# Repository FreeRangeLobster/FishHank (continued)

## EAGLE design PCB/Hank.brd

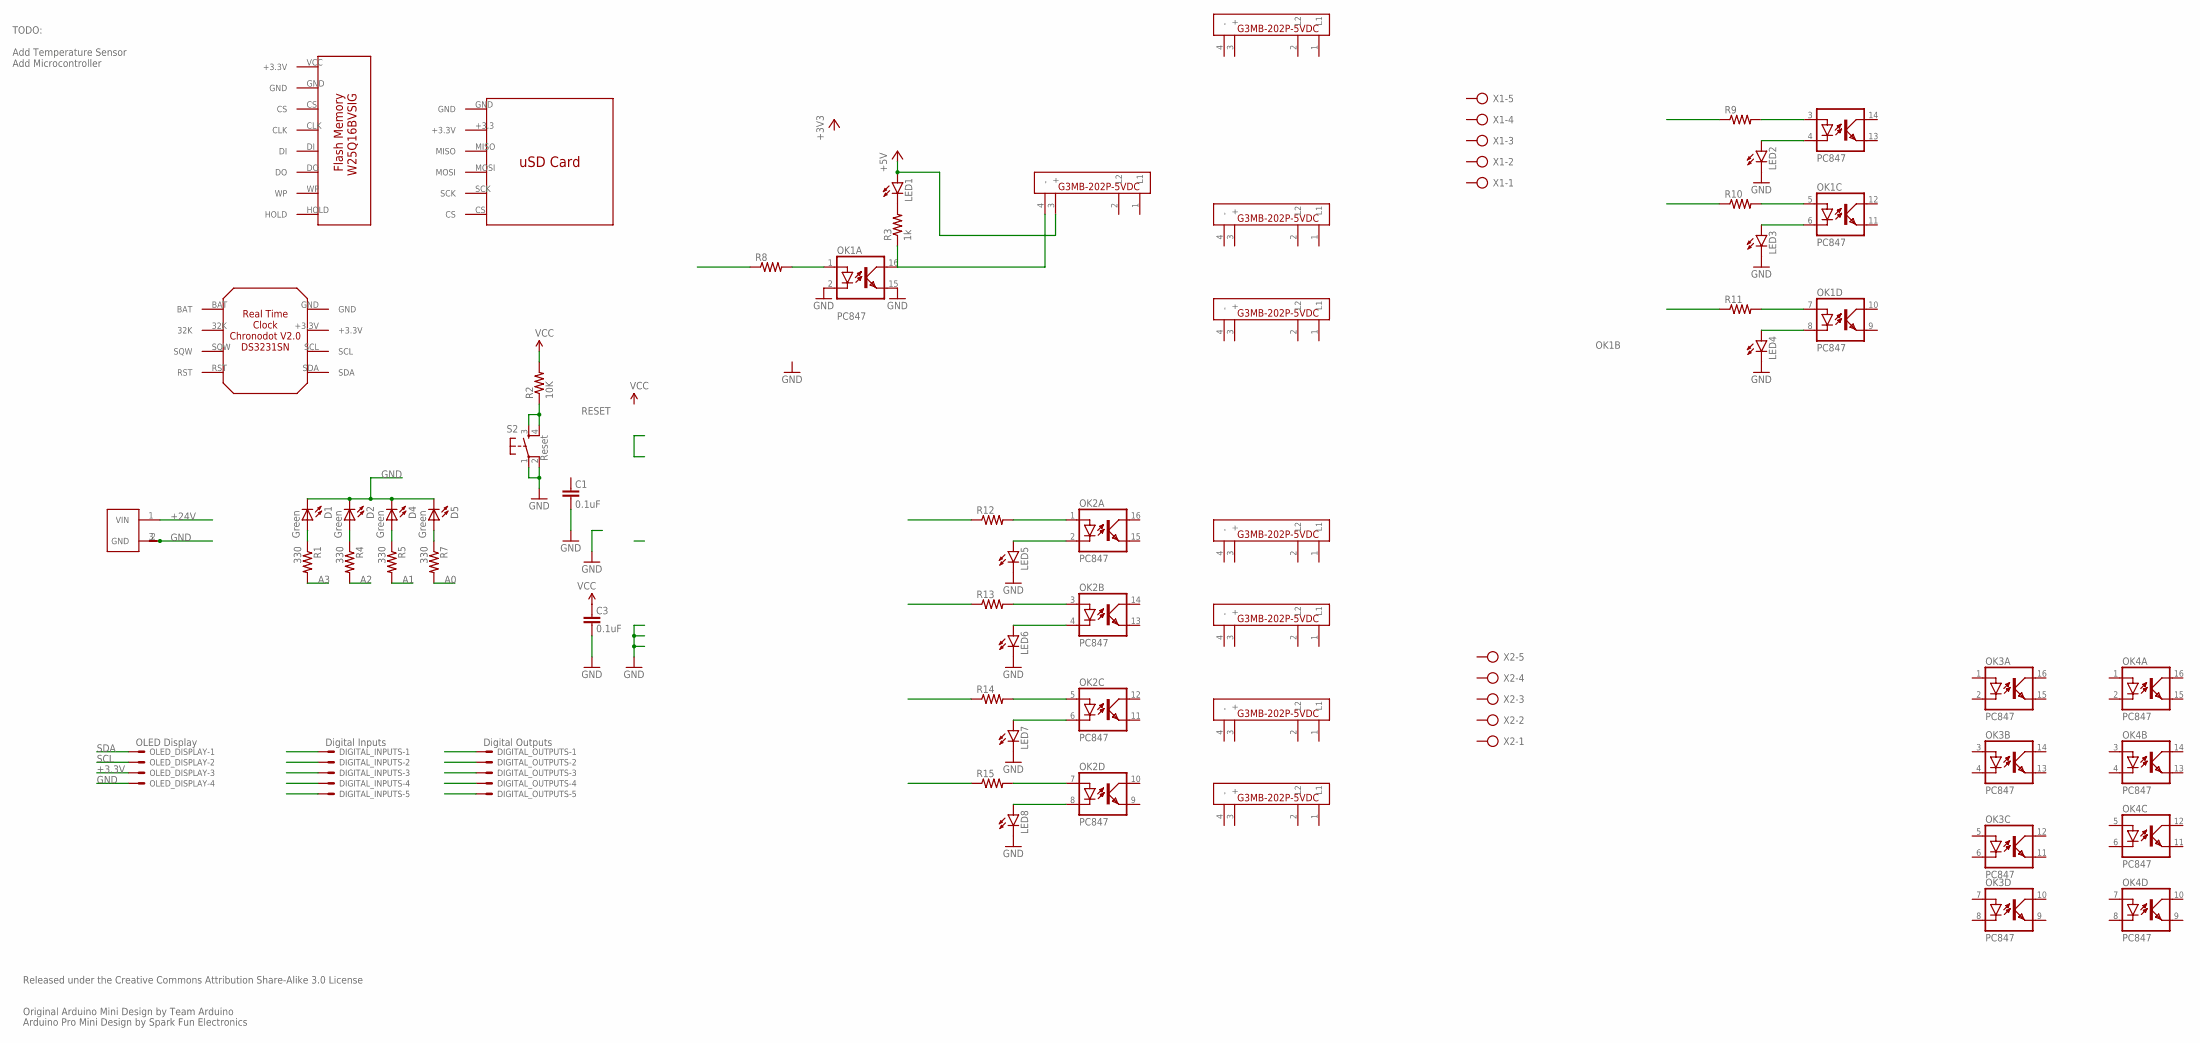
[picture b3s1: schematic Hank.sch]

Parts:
C1, C3: 0.1uF; C0603
D1, D2, D4, D5: Green; LED-0603
DIGITAL_INPUTS: Digital Inputs; 22-23-2051
DIGITAL_OUTPUTS: Digital Outputs; 22-23-2051
LED1, LED2, LED3, LED4, LED5, LED6, LED7, LED8: LED3MM
OK1, OK2, OK3, OK4: PC847; DIL16
OLED_DISPLAY: OLED Display; 22-23-2041
R1, R4, R5, R7: 330; R0603
R2: 10K; R0603
R3: 1k; 0207/10
R8, R9, R10, R11, R12, R13, R14, R15: R-US_0207/10; 0207/10
S2: Reset; TACTILE_SWITCH_SMD
U$1, U$7, U$8, U$9, U$10, U$11, U$12, U$13: SSR; SSR_FOOTPRINT
U$3: BARREL-3.5MM
U$4: FLASH_MEMORY; FLASHMEMORY_FOOTPRINT
U$6: RTC; RTC_FOOTPRINT
U$14: SD_CARD_READER; SD_CARD_READER_FOOTPRINT
X1, X2: AK300/5

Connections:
+3.3V: OLED_DISPLAY.3
+5V: LED1.A, U$7.3 (+)
+24V: U$3.1 (VIN)
A0: R7.2
A1: R5.2
A2: R4.2
A3: R1.2
GND: C1.1, C3.1, D1.C, D2.C, D4.C, D5.C, LED2.K (C), LED3.K (C), LED4.K (C), LED5.K (C), LED6.K (C), LED7.K (C), LED8.K (C), OK1.2 (C), OK1.15 (EMIT), OLED_DISPLAY.4, S2.1, S2.2, U$3.2 (GND__), U$3.3 (GND)
unnamed: D1.A, R1.1
unnamed: D2.A, R4.1
unnamed: D4.A, R5.1
unnamed: D5.A, R7.1
unnamed: LED4.A, OK1.8 (C)
unnamed: OK1.7 (A), R11.2
unnamed: OK1.1 (A), R8.2
unnamed: LED1.K (C), R3.2
unnamed: OK1.3 (A), R9.2
unnamed: LED2.A, OK1.4 (C)
unnamed: OK1.5 (A), R10.2
unnamed: LED3.A, OK1.6 (C)
unnamed: OK2.1 (A), R12.2
unnamed: OK2.3 (A), R13.2
unnamed: OK2.5 (A), R14.2
unnamed: OK2.7 (A), R15.2
unnamed: LED6.A, OK2.4 (C)
unnamed: LED5.A, OK2.2 (C)
unnamed: LED7.A, OK2.6 (C)
unnamed: LED8.A, OK2.8 (C)
unnamed: OK1.16 (COL), R3.1, U$7.4 (-)
RESET: R2.1, S2.3, S2.4
SCL: OLED_DISPLAY.2
SDA: OLED_DISPLAY.1
VCC: C3.2, R2.2

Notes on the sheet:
Released under the Creative Commons Attribution Share-Alike 3.0 License
TODO: Add Temperature Sensor Add Microcontroller
Original Arduino Mini Design by Team Arduino
Arduino Pro Mini Design by Spark Fun Electronics

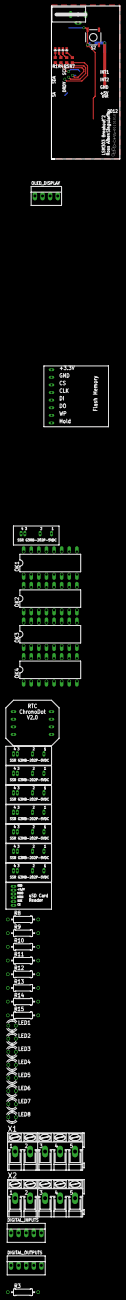
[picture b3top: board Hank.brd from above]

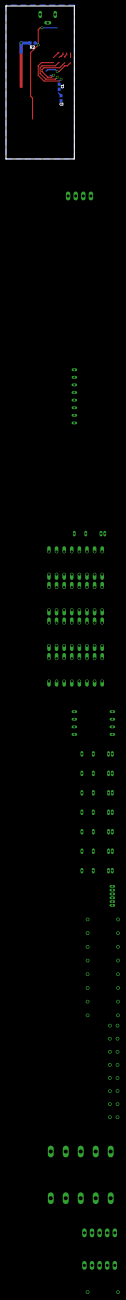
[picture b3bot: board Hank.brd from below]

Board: 2 copper layers, 22.8 x 51.1 mm, 50 parts (3 on the bottom side), 25 nets.

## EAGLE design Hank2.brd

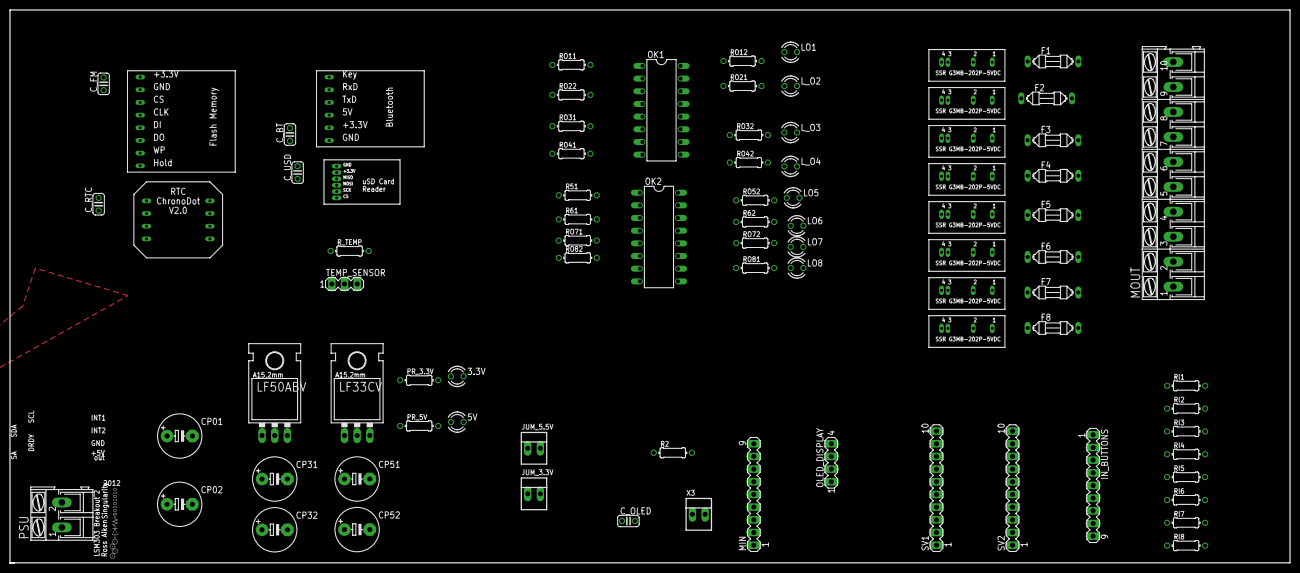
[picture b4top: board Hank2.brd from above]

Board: 2 copper layers, 256.5 x 110.8 mm, 84 parts (0 on the bottom side), 81 nets, no tracks yet.

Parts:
3.3V, 5V: LED3MM
CP01, CP31, CP51: 100u; E5-8,5
CP02, CP32, CP52: 100n; E5-8,5
C_BT: 0.1uF; C025-024X044
C_FM: 0.1uF; C025-024X044
C_OLED: 0.1uF; C025-024X044
C_RTC: 0.1uF; C025-024X044
C_USD: 0.1uF; C025-024X044
F1, F2, F3, F4, F5, F6, F7, F8: SM 092 A0 2A; PICOFUSE
IN_BUTTONS: MA09-1
JUM_3.3V, JUM_5.5V: 22-23-2021
LF33CV, LF50ABV: 78XXL
LO1, LO5, LO6, LO7, LO8: LED3MM
L_O2, L_O3, L_O4: LED3MM
MIN: MA09-1
MOUT: AK300/10
OK1, OK2: PC847; DIL16
OLED_DISPLAY: MA04-1
PR_3.3V, PR_5V: 1k; 0204/7
PSU: AK300/2
R2: 0204/7
R51, R61: 150; 0204/7
R62: 1k; 0204/7
RI1, RI2, RI3, RI4, RI5, RI6, RI7: 330; 0204/7
RI8: 0204/7
RO11, RO21, RO31, RO41, RO71, RO81: 150; 0204/7
RO12, RO22, RO42, RO52, RO72, RO82: 1k; 0204/7
RO32: 0204/7
R_TEMP: 4.7K; 0204/7
SSR1, SSR2, SSR3, SSR4, SSR5, SSR6, SSR7, SSR8: SSR; SSR_FOOTPRINT
SV1, SV2: MA10-1
TEMP_SENSOR: MA03-1
U$1: FLASH_MEMORY; FLASHMEMORY_FOOTPRINT
U$4: BLUETOOTH; BLUETOOTH_FOOTPRINT
U$6: RTC; RTC_FOOTPRINT
U$7: SD_CARD_READER; SD_CARD_READER_FOOTPRINT
X3: Auto_Manual; 22-23-2021

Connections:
+3V3: 3.3V.A, CP31.+, CP32.+, C_BT.1, C_FM.1, C_OLED.1, C_RTC.2, C_USD.1, IN_BUTTONS.1, JUM_5.5V.1, LF33CV.OUT, OLED_DISPLAY.3, R_TEMP.2, TEMP_SENSOR.3, U$1.HOLD, U$1.VCC, U$1.WP, U$4.+3.3, U$6.+3.3V, U$7.+3.3, X3.1
+5V: 5V.A, CP51.+, CP52.+, JUM_3.3V.1, LF50ABV.OUT, R62.2, RO12.2, RO22.2, RO32.2, RO42.2, RO52.2, RO72.2, RO82.2, SSR1.3, SSR2.3, SSR3.3, SSR4.3, SSR5.3, SSR6.3, SSR7.3, SSR8.3
AUTO: R2.2, SV2.10, X3.2
CP12: CP01.+, CP02.+, LF33CV.IN, LF50ABV.IN, PSU.1
FLASH_CLK: SV2.2, U$1.CLK
FLASH_CS: SV2.1, U$1.CS
FLASH_DI: SV2.3, U$1.DI
FLASH_DO: SV2.4, U$1.DO
GND: CP01.-, CP02.-, CP31.-, CP32.-, CP51.-, CP52.-, C_BT.2, C_FM.2, C_OLED.2, C_RTC.1, C_USD.2, LF33CV.GND, LF50ABV.GND, MIN.1, OK1.9, OK1.11, OK1.13, OK1.15, OK2.9, OK2.11, OK2.13, OK2.15, OLED_DISPLAY.4, PR_3.3V.1, PR_5V.1, PSU.2, R2.1, R51.1, R61.1, RO11.1, RO21.1, RO31.1, RO41.1, RO71.1, RO81.1, SV1.3, SV1.4, SV1.5, SV1.6, TEMP_SENSOR.1, U$1.GND, U$4.GND, U$6.GND, U$7.GND
IN1: IN_BUTTONS.2, RI1.1
IN2: IN_BUTTONS.3, RI2.1
IN3: IN_BUTTONS.4, RI3.1
IN4: IN_BUTTONS.5, RI4.1
IN5: IN_BUTTONS.6, RI5.1
IN6: IN_BUTTONS.7, RI6.1
IN7: IN_BUTTONS.8, RI7.1
IN8: IN_BUTTONS.9, RI8.1
L1-1: MOUT.1, SSR1.1, SSR2.1, SSR3.1, SSR4.1
L1-2: MOUT.6, SSR5.1, SSR6.1, SSR7.1, SSR8.1
L_O1: L_O2.K, OK1.14, SSR2.4
L_O3: L_O3.K, OK1.12, SSR3.4
MISO: SV2.5, U$7.MISO
MO1: F1.2, MOUT.2
MO2: F2.2, MOUT.3
MO3: F3.2, MOUT.4
MO4: F4.2, MOUT.5
MO5: F5.2, MOUT.7
MO6: F6.2, MOUT.8
MO7: F7.2, MOUT.9
MO8: F8.2, MOUT.10
MOSI: SV2.6, U$7.MOSI
MOUT2: F2.1, SSR2.2
MOUT3: F3.1, SSR3.2
MOUT4: F4.1, SSR4.2
MOUT5: F5.1, SSR5.2
MOUT6: F6.1, SSR6.2
MOUT7: F7.1, SSR7.2
MOUT8: F8.1, SSR8.2
unnamed: JUM_3.3V.2, SV1.1
unnamed: JUM_5.5V.2, SV1.2
unnamed: F1.1, SSR1.2
unnamed: 5V.K, PR_5V.2
unnamed: 3.3V.K, PR_3.3V.2
unnamed: RI1.2, RI2.2, RI3.2, RI4.2, RI5.2, RI6.2, RI7.2, RI8.2
unnamed: LO5.A, RO52.1
unnamed: LO5.K, OK2.16, SSR5.4
unnamed: OK2.2, R51.2
unnamed: LO6.A, R62.1
unnamed: LO6.K, OK2.14, SSR6.4
unnamed: OK2.4, R61.2
unnamed: LO7.A, RO72.1
unnamed: LO7.K, OK2.12, SSR7.4
unnamed: OK2.6, RO71.2
unnamed: LO8.A, RO82.1
unnamed: LO8.K, OK2.10, SSR8.4
unnamed: OK2.8, RO81.2
unnamed: LO1.A, RO12.1
unnamed: LO1.K, OK1.16, SSR1.4
unnamed: OK1.2, RO11.2
unnamed: L_O2.A, RO22.1
unnamed: OK1.4, RO21.2
unnamed: L_O3.A, RO32.1
unnamed: OK1.6, RO31.2
unnamed: L_O4.A, RO42.1
unnamed: L_O4.K, OK1.10, SSR4.4
unnamed: OK1.8, RO41.2
OUT1: MIN.2, OK1.1
OUT2: MIN.3, OK1.3
OUT3: MIN.4, OK1.5
OUT4: MIN.5, OK1.7
OUT5: MIN.6, OK2.1
OUT6: MIN.7, OK2.3
OUT7: MIN.8, OK2.5
OUT8: MIN.9, OK2.7
SCK: SV2.7, U$7.SCK
SCL: OLED_DISPLAY.1, U$6.SCL
SDA: OLED_DISPLAY.2, U$6.SDA
SD_CS: SV2.8, U$7.CS
SERIAL_RXD: SV1.7, U$4.RXD
SERIAL_TXD: SV1.8, U$4.TXD
TEMP_SEN: R_TEMP.1, SV2.9, TEMP_SENSOR.2

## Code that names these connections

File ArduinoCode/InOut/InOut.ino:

/*
 * Developed by JVivas to be used in the FishHank project 
 * github.com/freerangelobster
 * 15/4/2020
 * juanpadillavivas@gmail.com
 * Schecdule of outputs/inputs
 * Inputs A5,A4,A3,A2,A1,A0,D13,D12
 * Outputs D2,D3,D4,D5,D6,B0,B1,B2
 * New Data B4
 * Tx/RxD0,D1
 * Pinout ATMEga328P//http://www.hobbytronics.co.uk/arduino-atmega328-pinout
*/


//Outputs
#define Out1  2 //D2
#define Out2  3 //D3
#define Out3  4 //D4
#define Out4  5 //D5
#define Out5  6 //D6
#define Out6  7 //D6
#define Out7  8 //B0
#define Out8  9 //B1
//New Data Available
#define NewDataAvailable  10 //B2

//Inputs
#define In1 A5
#define In2 A4
#define In3 A3
#define In4 A2
#define In5 A1
#define In6 A0
#define In7 13 //B5
#define In8 12 //B4

int Inputs[8];
int Outputs[8];
int nDataAvailable;
int i;
String readString;
int nOutputNumber;

// the setup function runs once when you press reset or power the board
void setup() {
   Serial.begin(115200);
   Serial.print("Remote IO Restarted");
   Serial.print('\n');
   
   String sMsg;
    //outputs
    pinMode(Out1, OUTPUT); //D2
    pinMode(Out2, OUTPUT);
    pinMode(Out3, OUTPUT);
    pinMode(Out4, OUTPUT);
    pinMode(Out5, OUTPUT);
    pinMode(Out6, OUTPUT);
    pinMode(Out7, OUTPUT);
    pinMode(Out8, OUTPUT);
    pinMode(NewDataAvailable, OUTPUT); 
    //inputs
    pinMode(In1, INPUT);
    pinMode(In2, INPUT);
    pinMode(In3, INPUT);
    pinMode(In4, INPUT);
    pinMode(In5, INPUT);
    pinMode(In6, INPUT);
    pinMode(In7, INPUT);
    pinMode(In8, INPUT);
   //Setting the pull up resistors
    digitalWrite(In1, HIGH);
    digitalWrite(In2, HIGH);
    digitalWrite(In3, HIGH);
    digitalWrite(In4, HIGH);
    digitalWrite(In5, HIGH);
    digitalWrite(In6, HIGH);
    digitalWrite(In7, HIGH);
    digitalWrite(In8, HIGH);
}

void ClearLatchInputs(){
    for(i=0;i<8;i++){
          Inputs[i]=0;
    }
    digitalWrite(NewDataAvailable, LOW);
}


void executeCommand(String cmd)
{
    int nOutputNumber,i;
    String sOutputNumber;
    if (cmd == "?ID") Serial.println("FishHank I/O Microcontroller Ver 0.1");
    
    else if(cmd == "HELP"){
      Serial.println("?I = Returns the state of all inputs");
      Serial.println("?O = Returns the state of all outputs + New Data Available");
      Serial.println("!A0 = Resets all outputs");
      Serial.println("!11 = Sets Output 1 to high, there are 1-8 outputs");
      Serial.println("!10 = Resets Output 1 to Low, there are 1-8 outputs");
      Serial.println("ACK = Acknowledges the new data available and clears the pin flag");
    }
    
    
    else if (cmd == "?I"){
        Serial.print(Inputs[0]);
        Serial.print(Inputs[1]);
        Serial.print(Inputs[2]);
        Serial.print(Inputs[3]);
        Serial.print(Inputs[4]);
        Serial.print(Inputs[5]);
        Serial.print(Inputs[6]);
        Serial.print(Inputs[7]);
        Serial.print('\n');
        }

     
     else if (cmd == "?O"){
        //Serial.println(Outputs[0] + Outputs[1] + Outputs[2] + Outputs [3] + Outputs[4] + Outputs[5] + Outputs[6] + Outputs[7]);
        Serial.print(Outputs[0]);
        Serial.print(Outputs[1]);
        Serial.print(Outputs[2]);
        Serial.print(Outputs[3]);
        Serial.print(Outputs[4]);
        Serial.print(Outputs[5]);
        Serial.print(Outputs[6]);
        Serial.print(Outputs[7]);
        Serial.print(nDataAvailable);
        Serial.print('\n');
        }

     
     else if (cmd == "!A0"){
        //All to 0
        for(i=0;i<8;i++){
          Outputs[i]=0;
          }
        UpdateOutputs();  
        }

      
     else if (cmd.substring(0, 1) == "!"){
        //Captures in case there is a set of an output
        //Serial.println(cmd);
        //Serial.print("Setting Value to output:");
        sOutputNumber=cmd.substring(1, 2);
        nOutputNumber=sOutputNumber.toInt()-1;
        //Serial.println(sOutputNumber);
        if (cmd.substring(2, 3)=="1"){
          //Serial.println("Output High");
          Outputs[nOutputNumber]=1;
          }
        else{
          //Serial.println("Output Low");
          Outputs[nOutputNumber]=0;    
          }
        UpdateOutputs();
        Serial.print("OK");
        Serial.print('\n');     
        }


      else if (cmd == "ACK"){
          ClearLatchInputs();
          Serial.println("OK");   
         }

     
      else {
        Serial.print("NOK");
        Serial.print('\n');
      }
      
}


void UpdateOutputs(){
    if (Outputs[0]==1)digitalWrite(Out1, HIGH); else digitalWrite(Out1, LOW);
    if (Outputs[1]==1)digitalWrite(Out2, HIGH); else digitalWrite(Out2, LOW);
    if (Outputs[2]==1)digitalWrite(Out3, HIGH); else digitalWrite(Out3, LOW);
    if (Outputs[3]==1)digitalWrite(Out4, HIGH); else digitalWrite(Out4, LOW);
    if (Outputs[4]==1)digitalWrite(Out5, HIGH); else digitalWrite(Out5, LOW);
    if (Outputs[5]==1)digitalWrite(Out6, HIGH); else digitalWrite(Out6, LOW);
    if (Outputs[6]==1)digitalWrite(Out7, HIGH); else digitalWrite(Out7, LOW);
    if (Outputs[7]==1)digitalWrite(Out8, HIGH); else digitalWrite(Out8, LOW);
    }
  
void checkSerial(){
    if (!Serial.available()) return;
    char c = Serial.read();
    if ((c == '\n')||(c == '\r')) {
      Serial.print(readString);
      Serial.print('\n');
      executeCommand(readString);
      readString = "";    
    }
    else readString += c;
}

void CheckInputPressedAndLatch(){
    if (digitalRead (In1)==HIGH) {Inputs[0]=1;digitalWrite(NewDataAvailable, HIGH);}
    if (digitalRead (In2)==HIGH) {Inputs[1]=1;digitalWrite(NewDataAvailable, HIGH);}
    if (digitalRead (In3)==HIGH) {Inputs[2]=1;digitalWrite(NewDataAvailable, HIGH);}
    if (digitalRead (In4)==HIGH) {Inputs[3]=1;digitalWrite(NewDataAvailable, HIGH);}
    if (digitalRead (In5)==HIGH) {Inputs[4]=1;digitalWrite(NewDataAvailable, HIGH);}
    if (digitalRead (In6)==HIGH) {Inputs[5]=1;digitalWrite(NewDataAvailable, HIGH);}
    if (digitalRead (In7)==HIGH) {Inputs[6]=1;digitalWrite(NewDataAvailable, HIGH);}
    if (digitalRead (In8)==HIGH) {Inputs[7]=1;digitalWrite(NewDataAvailable, HIGH);}
}

void ReadOutputStatus(){
    Outputs[0] = digitalRead (Out1);
    Outputs[1] = digitalRead (Out2);
    Outputs[2] = digitalRead (Out3);
    Outputs[3] = digitalRead (Out4);
    Outputs[4] = digitalRead (Out5);
    Outputs[5] = digitalRead (Out6);
    Outputs[6] = digitalRead (Out7);
    Outputs[7] = digitalRead (Out8);
    nDataAvailable = digitalRead (NewDataAvailable);
}


// the loop function runs over and over again forever
void loop() {
  checkSerial();
  CheckInputPressedAndLatch();
  ReadOutputStatus();
  delay(1);                       
}

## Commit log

2019-12-18 initial project version
2019-12-27 finished library of sub assemblies, added ssr circuits
2019-12-28 Wired SSR circuits
2020-01-03 Added microcontroller connections
2020-01-06 Finished first draft of the schematic, started organising the PCB
2020-01-07 Placed components in PCB and exported some pics to verify footprints
2020-01-08 Adding Arduino micro to the libraries, it will handle buttons and outputs. communication intended to be serial
2020-01-09 Changed the interface of the SSR to Arduino. Added Arduino Sketch
2020-01-09 Adding Arduino Serial communication and tiding up code
2020-01-09 Tiding up files
2020-01-13 Changed v-regs and updated arduino program ready to test the ssrs
2020-01-14 Clarifyng ports in Arduino micro, more testing required
2020-01-21 Mods to the arduino code
2020-01-23 Tested the Atmega 328P and is fit for porpuse, Also got the Eagle library to add the Ic in the PCB
2020-01-24 Added Atmega 328-20P to the pcb and wired, still to be verified and tidied up
2020-01-25 Started arranging components in the PCB
2020-01-26 Added parts schedule
2020-01-27 Updating parts footprint in the brd
2020-01-30 Changed the VRegs and Added a crowbar circuit to handle overvoltage conditions
2020-01-31 Trying to set up the positions of the components in the PCB
2020-02-01 PCB routing session
2020-02-07 MAkng progress in the PCB
2020-02-18 Finilised the pcb and sent to production
2020-02-18 Added more info to the README file
2020-02-18 tidying up libraries
2020-02-18 Updated parts schedule
2020-02-18 Updated exports
2020-02-18 Updated PCB files
2020-02-18 Updated Production files and added the purchase order
2020-02-19 Added screengrab with the production process
2020-03-26 Added ESP32 Development file
2020-03-29 Added sample code for SD card reading using esp32, still to be tested
2020-04-13 Working on Arduino IO controller, work in progress to set up the outputs
2020-04-14 WIP arduino IO controller, to implement the input int and the ACK
2020-04-15 WIP arduino IO controller, code finished next test with the ESP32 to stablish comms
2020-04-17 Tested comminication with esp-arduino, only works if the ftdi is connected, need to find out why
2020-05-12 SD card sister board is not happy with 3.3V, needs at least 5 to operate properly. Temperature sensore tested succesfully
2020-06-10 updating Oled and RTC
2020-06-12 Merging RTC and OLED
2020-06-18 Oled showing current time
2020-06-22 Merging RTC, OLED and Temperature Sensor
2020-06-26 Added the SD card to the dev program
2020-06-27 Added Third Serial, 1 file in the spressif hardware core needs to be patched
2020-06-29 added the arduino version using from home pc to the readme file
2020-07-02 Serial_1 Working, this is to be connected to the ext Bluetooth
2020-07-05 Started development of configuration and supervisory app
2020-07-06 Starting to implement the state machine, added some functionality in the supervisory function
2020-07-08 Started to implement the serial command handler
2020-07-11 Laying out the config/supervisory c# app
2020-07-13 Laying out the supervisory user interface
2020-07-14 Designing the user interface for supervisory sys
2020-07-15 supervisory app UI
2020-07-15 Implemented serial Configuration and Open Port
2020-07-16 Addin field sto the terminal screen
2020-07-16 Basic Serial application ready for testing
2020-07-16 Added Settings to the Supervisory App
2020-07-16 Added sample code to browse and load file
2020-07-19 Added read .txt file function
2020-07-20 Improved the state machine of the embedded
2020-07-20 Sample xml file configuration
2020-07-21 RTC + OLed integration start
2020-07-23 Lib API handling using arduino IDE
2020-07-24 Trying to make buttons on the fly using an xml file. Will be used to send commands to the embedded system
2020-07-26 working on arduino libraries
2020-08-09 Setting up integration program for main controller
2020-08-10 Debugging communication with the Aux ucontroller from library
2020-08-25 Added Functions to handle Aux IO Board
2020-08-25 Modified the .net app font
2020-09-02 #integrating RTC and OLED to the main controller
2020-09-03 RTC and OLED integrated to main controller
2020-09-04 Modified the .net app to check config files
2020-09-08 Setting up table in oled display
2020-09-10 Setting up Display Status and time
2020-09-13 Testing Platform IO IDE
2020-09-14 Using platform IO to integrate main controller peripherals
2020-09-14 Added state machine structure
2020-09-14 Updated readme File
2020-09-17 Added SD card, implementing the state machine
2020-09-18 Testes state machine, ready to implement sd schedule and config options
2020-09-18 Show current time in display implemented
2020-09-20 Getting pinout of the system and updating README file
2020-09-21 Created pin out file for the esp32 used in this application
2020-09-22 updating README file
2020-09-23 Added Temperature sensor
2020-09-23 Added info on how to branch and merge
2020-09-24 Working on the Supervisory application
2020-09-25 Working on binding MVVM with the application
2020-09-25 Adding info to the supervosory app
2020-09-29 Tiding up front end
2020-09-30 Tiding up front end and ucontroller test program
2020-10-01 Tidying up serial communication app
2020-10-04 Adding commands to application and creating a class create commands dinamically
2020-10-07 Supervisory App usable, there is room for improvement
2020-10-12 Added functionality to the supervisory and to the embedded side
2020-10-12 Updated TODO lists in md file
2020-10-14 Developing check Event function, partially works but there is too much comms with aux board, needs improvement
2020-10-16 Added function to format time to be used in the search event
2020-10-19 Event finder working and running wit RTC clock
2020-10-19 Showing Uncle Raja
2020-10-20 Scheduler working and Supervisory working. Both in minimum functionality
2020-10-20 Scheduler working and Supervisory working. Both in minimum functionality-Merging
2020-10-20 Added Manual Override Outputs from supervisory
2020-10-27 tiding up the embedded program
2020-10-27 Adding Event Find for all days
2020-11-02 Support to All days event
2020-11-02 Updating status of the readme file
2020-11-09 Added functionality to read SD card configuration
2020-11-11 Changing code of IO controller, when input activated output will be activated
2020-11-12 Finished the IO Aux Firmware
2020-12-30 Testing MQTT using Mosquitto and NodeRed- Interesting Results
2021-01-01 trying more stuff in node-red, aiming to add it to the main controller
2021-01-04 Setting up node red stuff
2021-01-18 Modifying bluetooth communication
2021-01-19 Testing system
2021-01-21 Testing embedded system-ongoing
2021-01-22 tiding up code
2021-01-25 Fixed bug of the display showing wrong outputs
2021-01-25 Updated TODO List
2021-01-26 General Tidy up
2021-01-27 Added Auto/Manual Functionality, checked and updated pins, Increased the size of the form in the supervisory
2021-01-27 updated name of pin
2021-02-09 updated ReadME todo list
2021-02-09 Mods to PCB
2021-02-09 Added ESP32Dev Kit library to PCB
2021-02-11 Mods added to pcb finished, now route the PCB
2021-02-11 Changes to the transistorss footprint, ready to route
2021-02-11 routing
